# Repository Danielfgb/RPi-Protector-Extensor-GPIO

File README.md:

# RPi-Protector-Extensor-GPIO
Este proyecto consiste en un módulo diseñado para proteger los pines GPIO de la Raspberry Pi y extender su funcionalidad. El módulo incluye protecciones con diodos Zener y resistencias, un extensor de pines GPIO, la capacidad de conectar un módulo relé, y un módulo de reloj en tiempo real (RTC) DS3231.

## Características:

- Protección de GPIO: Cada pin GPIO está protegido con un diodo Zener y una resistencia de 330 ohms, protegiendo los pines de la Raspberry Pi contra sobretensiones y corrientes excesivas.
- Extensión de Pines GPIO: Se incluye un extensor de pines GPIO que permite la conexión de más dispositivos o módulos adicionales.
Compatibilidad con Módulo Relé.
- RTC DS3231: Se ha agregado un módulo de reloj en tiempo real (RTC) DS3231 para mantener el tiempo con alta precisión incluso cuando la Raspberry Pi está apagada.
- Indicadores LED: Se incluyen LEDs de estado en los pines GPIO sin un consumo excesivo de corriente.

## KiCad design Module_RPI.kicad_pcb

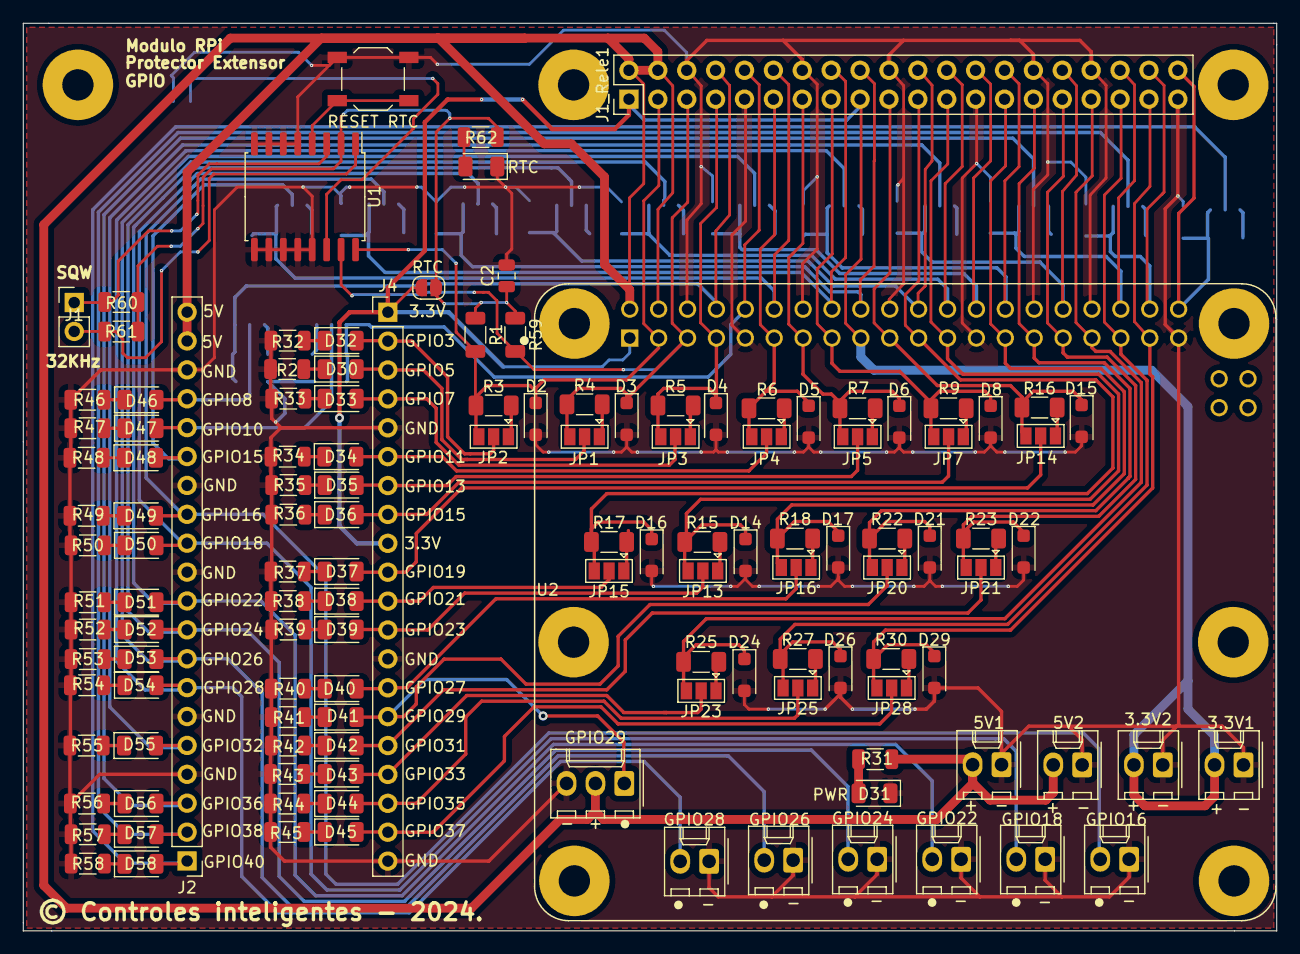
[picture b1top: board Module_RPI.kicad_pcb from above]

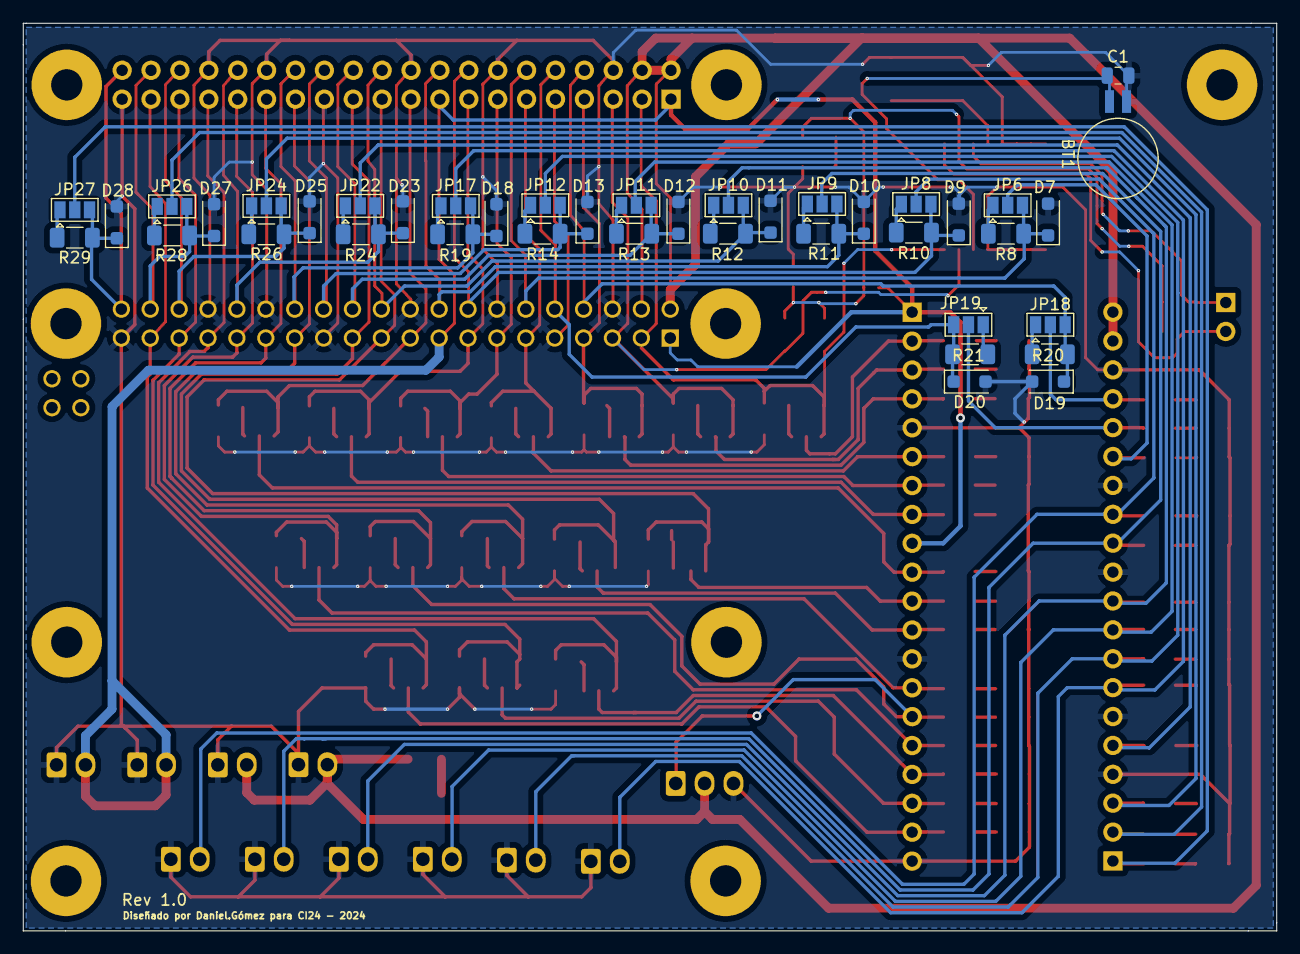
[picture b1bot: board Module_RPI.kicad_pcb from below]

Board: 2 copper layers, 110.2 x 79.8 mm, 170 parts (41 on the bottom side), 122 nets.

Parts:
3.3V1, 3.3V2, 5V1, 5V2: Conn_01x02; Molex_KK-254_AE-6410-02A_1x02_P2.54mm_Vertical
BT1: Battery; BatteryHolder_Seiko_MS621F
C1, C2: 100nF; C_0805_2012Metric
D2, D3, D4, D5, D6, D7, D8, D9, D10, D11, D12, D13, D14, D15, D16, D17, D18, D19, D20, D21, D22, D23, D24, D25, D26, D27, D28, D29: BZT52Bxx; D_SOD-123F
D30, D31, D32, D33, D34, D35, D36, D37, D38, D39, D40, D41, D42, D43, D44, D45, D46, D47, D48, D49, D50, D51, D52, D53, D54, D55, D56, D57, D58: LED; LED_1206_3216Metric
GPIO16, GPIO18, GPIO22, GPIO24, GPIO26, GPIO28: Conn_01x02; Molex_KK-254_AE-6410-02A_1x02_P2.54mm_Vertical
GPIO29: Conn_01x03; Molex_KK-254_AE-6410-03A_1x03_P2.54mm_Vertical
J1: Conn_01x02_Pin; PinHeader_1x02_P2.54mm_Vertical
J1_Rele1: Conn_02x20_Odd_Even; PinHeader_2x20_P2.54mm_Vertical
J2, J4: Conn_01x20; PinHeader_1x20_P2.54mm_Vertical
JP1, JP2, JP3, JP4, JP5, JP6, JP7, JP8, JP9, JP10, JP11, JP12, JP13, JP14, JP15, JP16, JP17, JP18, JP19, JP20, JP21, JP22, JP23, JP24, JP25, JP26, JP27, JP28: Jumper_3_Bridged12; SolderJumper-3_P1.3mm_Open_Pad1.0x1.5mm
R1, R59: 4.7K; R_1206_3216Metric
R2, R32, R33, R34, R35, R36, R37, R38, R39, R40, R41, R42, R43, R44, R45, R46, R47, R48, R49, R50, R51, R52, R53, R54, R55, R56, R57, R58, R60, R61, R62: 10K; R_1206_3216Metric
R3, R4, R5, R6, R7, R8, R9, R10, R11, R12, R13, R14, R15, R16, R17, R18, R19, R20, R21, R22, R23, R24, R25, R26, R27, R28, R29, R30: 330R; R_1206_3216Metric_Pad1.30x1.75mm_HandSolder
R31: 1K; R_1206_3216Metric
RESET RTC: SW_Push; SW_SPST_TL3342
RTC: LED; LED_1206_3216Metric
RTC#2: Jumper_2_Open; SolderJumper-2_P1.3mm_Open_RoundedPad1.0x1.5mm
U1: DS3231M; SOIC-16W_7.5x10.3mm_P1.27mm
U2: RASPBERRY_PI_4B_4GB; MODULE_RASPBERRY_PI_4B_4GB

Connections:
3.3V: 3.3V1.2, 3.3V2.2, J1_Rele1.1, J1_Rele1.17, J4.1, J4.9, RTC#2.2 (B), U2.1 (3V3), U2.17 (3V3)
5V: 5V1.2, 5V2.2, GPIO29.2, J1_Rele1.2, J1_Rele1.4, J2.19, J2.20, R31.1, U2.2 (5V), U2.4 (5V)
32KHz: J1.2, R61.2, U1.1 (32KHZ)
BAT: BT1.1 (+), C1.1, U1.14 (VBAT)
GND: 3.3V1.1, 3.3V2.1, 5V1.1, 5V2.1, BT1.2 (-), C1.2, C2.2, D2.2 (A), D3.2 (A), D4.2 (A), D5.2 (A), D6.2 (A), D7.2 (A), D8.2 (A), D9.2 (A), D10.2 (A), D11.2 (A), D12.2 (A), D13.2 (A), D14.2 (A), D15.2 (A), D16.2 (A), D17.2 (A), D18.2 (A), D19.2 (A), D20.2 (A), D21.2 (A), D22.2 (A), D23.2 (A), D24.2 (A), D25.2 (A), D26.2 (A), D27.2 (A), D28.2 (A), D29.2 (A), D31.1 (K), GPIO16.1, GPIO18.1, GPIO22.1, GPIO24.1, GPIO26.1, GPIO28.1, GPIO29.3, J1_Rele1.6, J1_Rele1.9, J1_Rele1.14, J1_Rele1.20, J1_Rele1.25, J1_Rele1.30, J1_Rele1.34, J1_Rele1.39, J2.4, J2.6, J2.11, J2.14, J2.18, J4.5, J4.13, J4.20, R2.2, R32.2, R33.2, R34.2, R35.2, R36.2, R37.2, R38.2, R39.2, R40.2, R41.2, R42.2, R43.2, R44.2, R45.2, R46.2, R47.2, R48.2, R49.2, R50.2, R51.2, R52.2, R53.2, R54.2, R55.2, R56.2, R57.2, R58.2, RESET RTC.2, RTC.1 (K), U1.5 (GND), U1.6 (GND), U1.7 (GND), U1.8 (GND), U1.9 (GND), U1.10 (GND), U1.11 (GND), U1.12 (GND), U1.13 (GND), U2.6 (GND), U2.9 (GND), U2.14 (GND), U2.20 (GND), U2.25 (GND), U2.30 (GND), U2.34 (GND), U2.39 (GND)
GPIO_3: D2.1 (K), J1_Rele1.3, JP2.3 (B), R1.2, R3.2, U1.16 (SCL), U2.3 (GPIO2/SDA1)
GPIO_3_P: D32.2 (A), J4.2, JP2.2 (C)
GPIO_5: D3.1 (K), J1_Rele1.5, JP1.3 (B), R4.2, R59.2, U1.15 (SDA), U2.5 (GPIO3/SCL1)
GPIO_5_P: D30.2 (A), J4.3, JP1.2 (C)
GPIO_7: D4.1 (K), J1_Rele1.7, JP3.3 (B), R5.2, U2.7 (GPIO4/GPIO_GCKL)
GPIO_7_P: D33.2 (A), J4.4, JP3.2 (C)
GPIO_8: D19.1 (K), J1_Rele1.8, JP18.3 (B), R20.2, U2.8 (GPIO14/TXD0)
GPIO_8_P: D46.2 (A), J2.17, JP18.2 (C)
GPIO_10: D20.1 (K), J1_Rele1.10, JP19.3 (B), R21.2, U2.10 (GPIO15/RXD0)
GPIO_10_P: D47.2 (A), J2.16, JP19.2 (C)
GPIO_11: D5.1 (K), J1_Rele1.11, JP4.3 (B), R6.2, U2.11 (GPIO17/GPIO_GEN0)
GPIO_11_P: D34.2 (A), J4.6, JP4.2 (C)
GPIO_12: D7.1 (K), J1_Rele1.12, JP6.3 (B), R8.2, U2.12 (GPIO18/GPIO_GEN1)
GPIO_12_P: D48.2 (A), J2.15, JP6.2 (C)
GPIO_13: D6.1 (K), J1_Rele1.13, JP5.3 (B), R7.2, U2.13 (GPIO27/GPIO_GEN2)
GPIO_13_P: D35.2 (A), J4.7, JP5.2 (C)
GPIO_15: D8.1 (K), J1_Rele1.15, JP7.3 (B), R9.2, U2.15 (GPIO22/GPIO_GEN3)
GPIO_15_P: D36.2 (A), J4.8, JP7.2 (C)
GPIO_16: D9.1 (K), J1_Rele1.16, JP8.3 (B), R10.2, U2.16 (GPIO23/GPIO_GEN4)
GPIO_16_P: D49.2 (A), GPIO16.2, J2.13, JP8.2 (C)
GPIO_18: D10.1 (K), J1_Rele1.18, JP9.3 (B), R11.2, U2.18 (GPIO24/GPIO_GEN5)
GPIO_18_P: D50.2 (A), GPIO18.2, J2.12, JP9.2 (C)
GPIO_19: D15.1 (K), J1_Rele1.19, JP14.3 (B), R16.2, U2.19 (GPIO10/SPI_MOSI)
GPIO_19_P: D37.2 (A), J4.10, JP14.2 (C)
GPIO_21: D16.1 (K), J1_Rele1.21, JP15.3 (B), R17.2, U2.21 (GPIO9/SPI_MISO)
GPIO_21_P: D38.2 (A), J4.11, JP15.2 (C)
GPIO_22: D11.1 (K), J1_Rele1.22, JP10.3 (B), R12.2, U2.22 (GPIO25/GPIO_GEN6)
GPIO_22_P: D51.2 (A), GPIO22.2, J2.10, JP10.2 (C)
GPIO_23: D14.1 (K), J1_Rele1.23, JP13.3 (B), R15.2, U2.23 (GPIO11/SPI_SCLK)
GPIO_23_P: D39.2 (A), J4.12, JP13.2 (C)
GPIO_24: D12.1 (K), J1_Rele1.24, JP11.3 (B), R13.2, U2.24 (GPIO8/~SPI_CE0)
GPIO_24_P: D52.2 (A), GPIO24.2, J2.9, JP11.2 (C)
GPIO_26: D13.1 (K), J1_Rele1.26, JP12.3 (B), R14.2, U2.26 (GPIO7/~SPI_CE1)
GPIO_26_P: D53.2 (A), GPIO26.2, J2.8, JP12.2 (C)
GPIO_27: D17.1 (K), J1_Rele1.27, JP16.3 (B), R18.2, U2.27 (ID_SD)
GPIO_27_P: D40.2 (A), J4.14, JP16.2 (C)
GPIO_28: D18.1 (K), J1_Rele1.28, JP17.3 (B), R19.2, U2.28 (ID_SC)
GPIO_28_P: D54.2 (A), GPIO28.2, J2.7, JP17.2 (C)
GPIO_29: D21.1 (K), J1_Rele1.29, JP20.3 (B), R22.2, U2.29 (GPIO5)
GPIO_29_P: D41.2 (A), GPIO29.1, J4.15, JP20.2 (C)
GPIO_31: D22.1 (K), J1_Rele1.31, JP21.3 (B), R23.2, U2.31 (GPIO6)
GPIO_31_P: D42.2 (A), J4.16, JP21.2 (C)
GPIO_32: D23.1 (K), J1_Rele1.32, JP22.3 (B), R24.2, U2.32 (GPIO12)
GPIO_32_P: D55.2 (A), J2.5, JP22.2 (C)
GPIO_33: D24.1 (K), J1_Rele1.33, JP23.3 (B), R25.2, U2.33 (GPIO13)
GPIO_33_P: D43.2 (A), J4.17, JP23.2 (C)
GPIO_35: D26.1 (K), J1_Rele1.35, JP25.3 (B), R27.2, U2.35 (GPIO19)
GPIO_35_P: D44.2 (A), J4.18, JP25.2 (C)
GPIO_36: D25.1 (K), J1_Rele1.36, JP24.3 (B), R26.2, U2.36 (GPIO16)
GPIO_36_P: D56.2 (A), J2.3, JP24.2 (C)
GPIO_37: D29.1 (K), J1_Rele1.37, JP28.3 (B), R30.2, U2.37 (GPIO26)
GPIO_37_P: D45.2 (A), J4.19, JP28.2 (C)
GPIO_38: D27.1 (K), J1_Rele1.38, JP26.3 (B), R28.2, U2.38 (GPIO20)
GPIO_38_P: D57.2 (A), J2.2, JP26.2 (C)
GPIO_40: D28.1 (K), J1_Rele1.40, JP27.3 (B), R29.2, U2.40 (GPIO21)
GPIO_40_P: D58.2 (A), J2.1, JP27.2 (C)
unnamed: R62.2, RTC.2 (A)
unnamed: D30.1 (K), R2.1
unnamed: D31.2 (A), R31.2
unnamed: D32.1 (K), R32.1
unnamed: D33.1 (K), R33.1
unnamed: D34.1 (K), R34.1
unnamed: D35.1 (K), R35.1
unnamed: D36.1 (K), R36.1
unnamed: D37.1 (K), R37.1
unnamed: D38.1 (K), R38.1
unnamed: D39.1 (K), R39.1
unnamed: D40.1 (K), R40.1
unnamed: D41.1 (K), R41.1
unnamed: D42.1 (K), R42.1
unnamed: D43.1 (K), R43.1
unnamed: D44.1 (K), R44.1
unnamed: D45.1 (K), R45.1
unnamed: D46.1 (K), R46.1
unnamed: D47.1 (K), R47.1
unnamed: D48.1 (K), R48.1
unnamed: D49.1 (K), R49.1
unnamed: D50.1 (K), R50.1
unnamed: D51.1 (K), R51.1
unnamed: D52.1 (K), R52.1
unnamed: D53.1 (K), R53.1
unnamed: D54.1 (K), R54.1
unnamed: D55.1 (K), R55.1
unnamed: D56.1 (K), R56.1
unnamed: D57.1 (K), R57.1
unnamed: D58.1 (K), R58.1
unnamed: JP1.1 (A), R4.1
unnamed: JP2.1 (A), R3.1
unnamed: JP3.1 (A), R5.1
unnamed: JP4.1 (A), R6.1
unnamed: JP5.1 (A), R7.1
unnamed: JP6.1 (A), R8.1
unnamed: JP7.1 (A), R9.1
unnamed: JP8.1 (A), R10.1
unnamed: JP9.1 (A), R11.1
unnamed: JP10.1 (A), R12.1
unnamed: JP11.1 (A), R13.1
unnamed: JP12.1 (A), R14.1
unnamed: JP13.1 (A), R15.1
unnamed: JP14.1 (A), R16.1
unnamed: JP15.1 (A), R17.1
unnamed: JP16.1 (A), R18.1
unnamed: JP17.1 (A), R19.1
unnamed: JP18.1 (A), R20.1
unnamed: JP19.1 (A), R21.1
unnamed: JP20.1 (A), R22.1
unnamed: JP21.1 (A), R23.1
unnamed: JP22.1 (A), R24.1
unnamed: JP23.1 (A), R25.1
unnamed: JP24.1 (A), R26.1
unnamed: JP25.1 (A), R27.1
unnamed: JP26.1 (A), R28.1
unnamed: JP27.1 (A), R29.1
unnamed: JP28.1 (A), R30.1
unnamed: RESET RTC.1, U1.4 (~RST)
RTC: C2.1, R1.1, R59.1, R60.1, R61.1, R62.1, RTC#2.1 (A), U1.2 (VCC)
SQW: J1.1, R60.2, U1.3 (~INT/SQW)

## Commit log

2024-08-30 :sparkles: Archivos de diseño de PCB
2024-08-30 :sparkles: Gerber y lista de componentes
2024-09-02 Actualización Modulo RPI
2024-09-02 Actualización README
2024-09-02 Actualización archivo kicad

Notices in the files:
Module_RPI.kicad_pcb:
© Controles inteligentes - 2024.
